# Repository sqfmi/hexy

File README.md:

# Hexy

Inspired by [Mukesh Sankhla](https://www.youtube.com/c/MukeshSankhla)'s [HexMatrix](https://hackaday.io/project/173732-rgb-hexmatrix-iot-clock) project, this is a smaller version using 96 3.5x3.5MM RGB LEDs ([WS2812B-MINI](https://www.adafruit.com/product/2659))

## Hardware
All KiCad design files under MIT license

### BOM
- 1 x PCB
- 96 x [WS2812B-MINI](https://www.adafruit.com/product/2659)
- 1 x [TTGO T-DISPLAY](https://www.aliexpress.com/item/33048962331.html) (or any other microcontroller)
- 2 x [2.54MM SMD Pin Headers](https://www.digikey.com/product-detail/en/amphenol-icc-fci/10129380-906001ALF/609-10129380-906001ALFCT-ND/11630008) (You only need 3 pins connected i.e. DIN/VCC/GND but using a full row of 12 pins will mount more securely)

### Wiring Pattern
The LEDs are laid out in a zigzag pattern:

## Software
We used the [FastLED](https://github.com/FastLED/FastLED) library v3.3
- Set the data pin to **13** (or any other pin if you are using another microcontroller)
- Set the number of LEDs to **96**
- Set the LED Chipset to **WS2812B**

## Frame
For best visual results, 3D print the seperator grid [hexy-frame.stl](hexy-frame.stl) to keep the light from bleeding over. You will also need a piece of paper/acrylic glued on top to diffuse the light so each triangle cell looks nice and crisp [hexy-diffusion.dxf](hexy-diffusion.dxf)

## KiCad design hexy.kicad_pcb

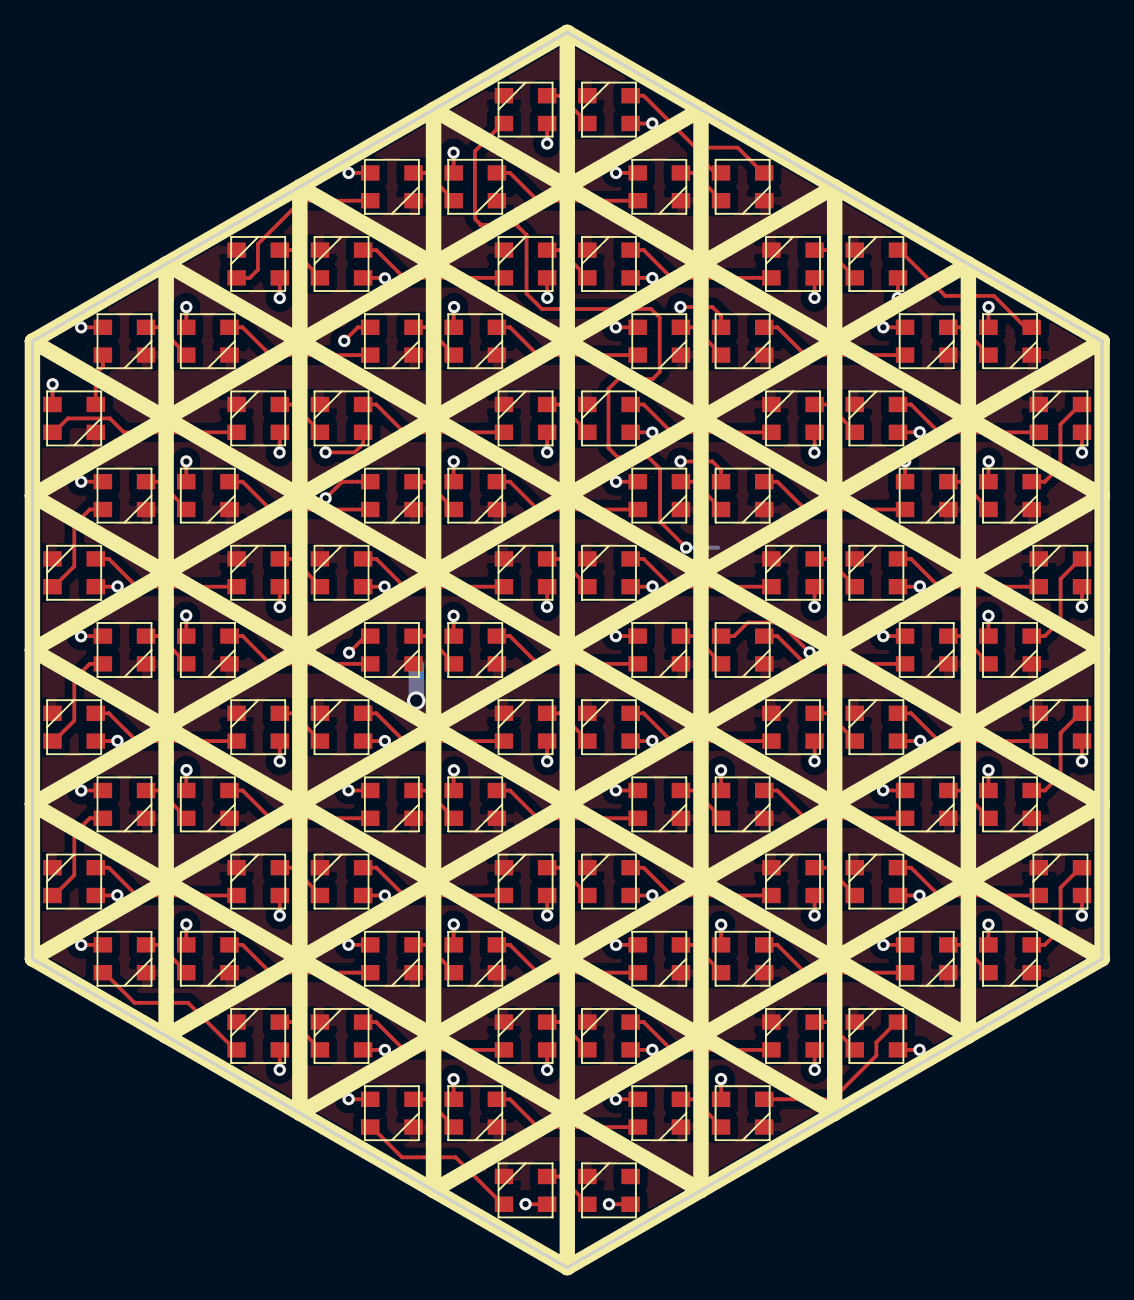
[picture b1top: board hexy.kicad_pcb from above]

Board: 2 copper layers, 69.3 x 80.0 mm, 97 parts (1 on the bottom side), 98 nets.

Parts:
D1, D2, D3, D4, D5, D6, D7, D8, D9, D10, D11, D12, D13, D14, D15, D16, D17, D18, D19, D20, D21, D22, D23, D24, D25, D26, D27, D28, D29, D30, D31, D32, D33, D34, D35, D36, D37, D38, D39, D40, D41, D42, D43, D44, D45, D46, D47, D48, D49, D50, D51, D52, D53, D54, D55, D56, D57, D58, D59, D60, D61, D62, D63, D64, D65, D66, D67, D68, D69, D70, D71, D72, D73, D74, D75, D76, D77, D78, D79, D80, D81, D82, D83, D84, D85, D86, D87, D88, D89, D90, D91, D92, D93, D94, D95, D96: WS2812B; WS2812B-MINI
TTGO T-DISPLAY: TTGO_T-DISPLAY; TTGO_T-DISPLAY_SMD

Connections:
DIN: D1.4, TTGO T-DISPLAY.8
GND: D1.3, D2.3, D3.3, D4.3, D5.3, D6.3, D7.3, D8.3, D9.3, D10.3, D11.3, D12.3, D13.3, D14.3, D15.3, D16.3, D17.3, D18.3, D19.3, D20.3, D21.3, D22.3, D23.3, D24.3, D25.3, D26.3, D27.3, D28.3, D29.3, D30.3, D31.3, D32.3, D33.3, D34.3, D35.3, D36.3, D37.3, D38.3, D39.3, D40.3, D41.3, D42.3, D43.3, D44.3, D45.3, D46.3, D47.3, D48.3, D49.3, D50.3, D51.3, D52.3, D53.3, D54.3, D55.3, D56.3, D57.3, D58.3, D59.3, D60.3, D61.3, D62.3, D63.3, D64.3, D65.3, D66.3, D67.3, D68.3, D69.3, D70.3, D71.3, D72.3, D73.3, D74.3, D75.3, D76.3, D77.3, D78.3, D79.3, D80.3, D81.3, D82.3, D83.3, D84.3, D85.3, D86.3, D87.3, D88.3, D89.3, D90.3, D91.3, D92.3, D93.3, D94.3, D95.3, D96.3, TTGO T-DISPLAY.14
unnamed: D1.2, D2.4
unnamed: D2.2, D3.4
unnamed: D3.2, D4.4
unnamed: D4.2, D5.4
unnamed: D5.2, D6.4
unnamed: D6.2, D7.4
unnamed: D7.2, D8.4
unnamed: D8.2, D9.4
unnamed: D10.2, D11.4
unnamed: D9.2, D10.4
unnamed: D11.2, D12.4
unnamed: D12.2, D13.4
unnamed: D13.2, D14.4
unnamed: D14.2, D15.4
unnamed: D15.2, D16.4
unnamed: D16.2, D17.4
unnamed: D17.2, D18.4
unnamed: D18.2, D19.4
unnamed: D19.2, D20.4
unnamed: D20.2, D21.4
unnamed: D21.2, D22.4
unnamed: D22.2, D23.4
unnamed: D23.2, D24.4
unnamed: D24.2, D25.4
unnamed: D25.2, D26.4
unnamed: D26.2, D27.4
unnamed: D27.2, D28.4
unnamed: D28.2, D29.4
unnamed: D29.2, D30.4
unnamed: D30.2, D31.4
unnamed: D31.2, D32.4
unnamed: D32.2, D33.4
unnamed: D33.2, D34.4
unnamed: D34.2, D35.4
unnamed: D35.2, D36.4
unnamed: D36.2, D37.4
unnamed: D37.2, D38.4
unnamed: D38.2, D39.4
unnamed: D39.2, D40.4
unnamed: D40.2, D41.4
unnamed: D41.2, D42.4
unnamed: D42.2, D43.4
unnamed: D43.2, D44.4
unnamed: D44.2, D45.4
unnamed: D45.2, D46.4
unnamed: D46.2, D47.4
unnamed: D47.2, D48.4
unnamed: D48.2, D49.4
unnamed: D49.2, D50.4
unnamed: D50.2, D51.4
unnamed: D51.2, D52.4
unnamed: D52.2, D53.4
unnamed: D53.2, D54.4
unnamed: D54.2, D55.4
unnamed: D55.2, D56.4
unnamed: D56.2, D57.4
unnamed: D57.2, D58.4
unnamed: D58.2, D59.4
unnamed: D59.2, D60.4
unnamed: D60.2, D61.4
unnamed: D61.2, D62.4
unnamed: D62.2, D63.4
unnamed: D63.2, D64.4
unnamed: D64.2, D65.4
unnamed: D65.2, D66.4
unnamed: D66.2, D67.4
unnamed: D67.2, D68.4
unnamed: D68.2, D69.4
unnamed: D69.2, D70.4
unnamed: D70.2, D71.4
unnamed: D71.2, D72.4
unnamed: D72.2, D73.4
unnamed: D73.2, D74.4
unnamed: D74.2, D75.4
unnamed: D75.2, D76.4
unnamed: D76.2, D77.4
unnamed: D77.2, D78.4
unnamed: D78.2, D79.4
unnamed: D79.2, D80.4
unnamed: D80.2, D81.4
unnamed: D81.2, D82.4
unnamed: D82.2, D83.4
unnamed: D83.2, D84.4
unnamed: D84.2, D85.4
unnamed: D85.2, D86.4
unnamed: D86.2, D87.4
unnamed: D87.2, D88.4
unnamed: D88.2, D89.4
unnamed: D89.2, D90.4
unnamed: D90.2, D91.4
unnamed: D91.2, D92.4
unnamed: D92.2, D93.4
unnamed: D93.2, D94.4
unnamed: D94.2, D95.4
unnamed: D95.2, D96.4
VCC: D1.1, D2.1, D3.1, D4.1, D5.1, D6.1, D7.1, D8.1, D9.1, D10.1, D11.1, D12.1, D13.1, D14.1, D15.1, D16.1, D17.1, D18.1, D19.1, D20.1, D21.1, D22.1, D23.1, D24.1, D25.1, D26.1, D27.1, D28.1, D29.1, D30.1, D31.1, D32.1, D33.1, D34.1, D35.1, D36.1, D37.1, D38.1, D39.1, D40.1, D41.1, D42.1, D43.1, D44.1, D45.1, D46.1, D47.1, D48.1, D49.1, D50.1, D51.1, D52.1, D53.1, D54.1, D55.1, D56.1, D57.1, D58.1, D59.1, D60.1, D61.1, D62.1, D63.1, D64.1, D65.1, D66.1, D67.1, D68.1, D69.1, D70.1, D71.1, D72.1, D73.1, D74.1, D75.1, D76.1, D77.1, D78.1, D79.1, D80.1, D81.1, D82.1, D83.1, D84.1, D85.1, D86.1, D87.1, D88.1, D89.1, D90.1, D91.1, D92.1, D93.1, D94.1, D95.1, D96.1, TTGO T-DISPLAY.13
